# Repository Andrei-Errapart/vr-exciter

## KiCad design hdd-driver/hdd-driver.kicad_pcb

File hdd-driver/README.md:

# HDD spindle driver board

A carrier PCB that screws to the underside of the gutted 3.5" hard drive. It
drives the spindle motor through the drive's own **spring contacts**, so the
magnet disc in `../disk/` can spin at 3000 rpm.

- **MCU:** WeAct Studio STM32G474CEU6 **Core Board** (the square 36 × 28 mm
  board), on sockets.
- **Motor driver:** SimpleFOC Mini v1.0 (TI DRV8313), on sockets, driven in
  3-PWM mode from TIM1.
- **Motor supply:** external 12 V on a screw terminal, or USB through an
  MT3608 boost module (5 V → 12 V). Jumper JP1 selects between them.
- **Supply monitor:** VM ÷ 11 into an ADC pin.
- **Current sensing:** VM bus current (INA181) and inline phase A/B current
  (two INA240), all into ADC pins.
- **Speed/angle pickup:** input for a VR (variable reluctance) pickup coil
  under the magnet disc, into a comparator and ADC pin.

KiCad 10 project: `hdd-driver.kicad_pro`. The schematic passes ERC with 0
violations. The PCB is fully routed: DRC reports 0 unconnected items. The
remaining DRC errors are the C2/U2 courtyard overlap and U3 in the edge
keepout, plus silkscreen warnings.

## Files

| Path | Content |
|------|---------|
| `hdd-driver.kicad_sch`, `.kicad_pcb`, `.kicad_pro` | Schematic and PCB. They were generated once by script and are now the source: edit them in KiCad. |
| `sym-lib-table`, `fp-lib-table` | Project libraries `hdd-driver` (paths use `${KIPRJMOD}`) |
| `lib/hdd-driver.kicad_sym` | Symbols: `WeAct_STM32G474_CoreBoard`, `SimpleFOC_Mini_v1.0`, `MT3608_Boost_Module`, `HDD_Motor_SpringContacts` |
| `lib/hdd-driver.pretty/` | Footprints for those parts, plus `MountingHole_2.4mm_M2_Pad` and `MountingHole_3.2mm_M3_Pad` |
| `lib/3d/*.step` | Module models (WeAct, SimpleFOC Mini, MT3608) with pins-down headers |
| `lib/3d/src/` | WeAct's original STEP, the same STEP with its headers stripped, and the KiCad source boards the module models are exported from |
| `Export_HddDriver_V1_zip` | JLCPCB manufacturing package; see [Regenerating generated files](#regenerating-generated-files) |
| `scripts/export-test-model` | Fit-test 3D models; see [Checking the fit](#checking-the-fit) |
| `scripts/module-models/` | Regenerates `lib/3d/*.step` (`make-module-models`) |
| `scripts/library/` | Generators that made the symbols and footprints, plus a small S-expression helper. Rerunning them overwrites edits made in KiCad. |
| `scripts/photo/rectify_underside.py` | The photo measurement behind the board geometry |
| `doc/` | Images: candidate holes, outline options, final layout on the photo |

## Mechanics

### Drive frame

All drive positions are in a **drive frame**: a bottom view as photographed,
with the connector end at the top.

- **X** runs to the right from the drive's centre line.
- **Y** runs down from the connector end.
- The PCB's aux and grid origins sit at the drive-frame origin, which is
  KiCad position (150, 40) mm. Set the KiCad coordinate display to the grid
  origin and positions read directly in this frame.

The positions come from `../disk/hdd-photos/07-hdd-underside-width-ruler.jpg`.
That photo is taken at an angle, and its rulers lie about 26 mm below the
underside of the drive, so ruler scale is no use here (on the rectified image
the rulers read about 2 % short). Instead, the photo was rectified with a
homography fitted to the four **SFF-8301 bottom mounting holes**. Those holes
are 95.25 mm apart across the drive, 41.28 mm from the connector end, with
the second pair 44.45 mm further down. Expect about ±0.5 mm on the features
below. `scripts/photo/rectify_underside.py` has the method and the pixel
data.

| Feature | X | Y | Notes |
|---|---|---|---|
| Screw hole 2 | 16.69 | 15.29 | M2, holds the PCB |
| Screw hole 3 | 16.73 | 31.27 | M2, holds the PCB |
| Screw hole 7 | −9.05 | 56.92 | M2, holds the PCB **and** the spring-contact block |
| Screw hole 8 | 31.29 | 62.90 | M2, holds the PCB |
| Screw holes 1, 6 | −43.37 / −42.58 | 17.63 / 63.39 | Not used: a plain rectangle cannot reach them without a notch around SFF hole 4 |
| SFF holes 4, 5, 9, 10 | ±47.625 | 41.28 / 85.73 | Drive mounting holes (6-32) on the side rails; outside the PCB |
| Spring contacts 1–3 (tips) | −11.83 / −9.83 / −7.87 | 63.67 / 63.17 / 62.60 | 2.0 mm pitch, about 6.0 mm from screw 7, strip turned 13.5° |
| Spindle axis | 0.2 | 95.9 | The large circle (R ≈ 20) |

`doc/hdd-underside-candidate-holes.jpg` shows the hole numbering.

### PCB

- **Outline:** a plain rectangle, X −36…38 and Y 0…73 (74 × 73 mm), 1.6 mm
  thick. It started as option B in `doc/outline-options.jpg` (Y 12…88). The
  first test print showed that the bottom edge sat on the motor, so the
  outline moved 15 mm towards the connector end. It now ends about 3 mm short
  of the motor circle. The top edge used to reach 3 mm past the drive's
  connector end; it was cut back to sit flush with it. The sides still clear
  the rail bulges around SFF holes 4 and 5.
- **Edge keepout:** component courtyards stay 1 mm clear of the board edge.
  The rule area `EdgeKeepout` (a 1 mm frame inside the outline) and the
  custom rule in `hdd-driver.kicad_dru` enforce this in DRC. Footprints
  excluded from the BOM (the mounting holes and other copper-only parts) are
  exempt.
- **GND pours:** `GND_TOP` on F.Cu and `GND_BOTTOM` on B.Cu cover the whole
  board (0.3 mm clearance, thermal reliefs). The rule area
  `J2_SpringKeepout` (J2's B.CrtYd) keeps the bottom pour and vias away from
  the spring pads. 0.6/0.3 mm GND stitching vias run about every 5 mm round
  the edge and on a 10 mm grid inside, only where both pours have copper.
- **Mounting:** four M2 screws in holes 2, 3, 7 and 8. Holes are 2.4 mm
  (ISO 273 medium fit), plated with a 4.2 mm pad, and tied to GND.
- **Corner holes H4–H7:** M3 (3.2 mm, plated, 6.4 mm pad, on GND), 4 mm in
  from each edge, at X −32 / 34 and Y 4 / 69. They are optional: for rubber
  feet, or for spacers to a housing. H6/H7 courtyards are kept free of parts
  on both sides. Since the top edge was cut back, H4 and H5 overlap the
  courtyards of U1 (WeAct) and U3 (MT3608); DRC reports this, and it is
  still open.
- **Spring contacts:** footprint `HDD_SpringContacts_3P_P2.0mm`, placed on
  screw 7 and rotated 13.5°. Three 1.4 × 4.0 mm pads on **B.Cu**, the side
  facing the drive. The pad centres lie within 0.2 mm of the measured spring
  tips. Order the board with ENIG (gold) finish for these pads.
- **Modules** on top, away from the drive:
  - WeAct board at the top left, with its USB-C facing the left edge.
  - MT3608 upright at the right, between holes 2/3 and the edge.
  - SimpleFOC Mini in the lower middle, between the MT3608 and hole 8,
    turned 180°.
  - JP1 between the WeAct board and holes 2/3; C1 and C2 next to the
    SimpleFOC `+` pad.
  - The 12 V screw terminal J1 at the lower left, wire entry facing out,
    with D1 beside it.
- **Stacking heights:**
  - 2×12, 2×5, 1×3 and 1×1 female sockets: 8.5 mm.
  - Male header plastic on the modules: 2.54 mm.
  - So each module PCB sits 11.04 mm above the carrier.
  - The MT3608 sits on its pins, 2.54 mm above the carrier.
  - The highest point is the WeAct board, about 16 mm above the carrier's
    top surface; the MT3608 trimmer reaches about 15 mm.
  - The drive needs feet at least that high when it stands on its underside.

## Electronics

```
J1 12V IN ─ D1 SS54 ─┬─ +12V ── JP1.1 ┐
 (reverse polarity)  │                ├─ JP1.2 = VM ─┬─ RS1 20 mΩ ─ VM_DRV ─┬─ SimpleFOC "+" ── DRV8313 VM
                     │   VBOOST ─ JP1.3 ┘            │  (U4 INA181: I_BUS)  └─ C1 470 µF + C2 100 nF
                     │      ▲                        └─ R1 100k / R2 10k ─ VM_SENSE ─ PA0
                     │   U3 MT3608 (set to 12 V)
                     │      ▲
                     └─ D2 B5819W ─ VCC_MCU ─ WeAct VCC (LDO input, 3.3–20 V)
                                    ▲
                     USB VBUS ─ WeAct's own B5819W ┘
```

- **JP1 1-2:** the motor runs from the external 12 V. D2 also feeds the WeAct
  `VCC`, so the MCU runs without USB. WeAct's own VBUS diode keeps the 12 V
  away from the USB host.
- **JP1 2-3:** the motor runs from USB. WeAct `VCC` (VBUS minus a Schottky
  drop, about 4.6 V) feeds the MT3608, and its 12 V output becomes VM. **Set
  the trimmer to 12 V before fitting the jumper.** The DRV8313 needs
  VM ≥ 8 V (UVLO), so USB 5 V can't drive it directly. USB current (and the
  1 A WeAct diode) limit the motor power in this mode.

| Signal | MCU pin (WeAct header) | SimpleFOC Mini | Notes |
|---|---|---|---|
| DRV_IN1 | PA8, TIM1_CH1 AF6 (P1.10) | IN1 (H1 pin 3) | |
| DRV_IN2 | PA9, TIM1_CH2 AF6 (P1.11) | IN2 (5) | |
| DRV_IN3 | PA10, TIM1_CH3 AF6 (P1.12) | IN3 (7) | |
| DRV_EN | PB12 (P1.5) | EN (9) | 10 kΩ into EN1–3, 100 kΩ pull-downs: the driver is off at reset |
| DRV_nFAULT | PB13 (P1.6) | nFT (10) | Open drain, 10 kΩ pull-up on the module |
| DRV_nSLEEP | PB14 (P1.7) | nSP (8) | |
| DRV_nRESET | PB15 (P1.8) | nRT (6) | |
| VM_SENSE | PA0, ADC1_IN1 (P2.20) | — | VM / 11; 35 V gives 3.18 V |
| PH_A/B/C | — | M1/M2/M3 | To the spring pads, A and B through RS2/RS3. Phase order only sets the direction of rotation. |
| I_A | PA2, ADC1_IN3 (P2.18) | — | Phase A current (U5 INA240A1, RS2 20 mΩ): 1.65 V − 0.4 V/A (inverted, see below), ±4 A |
| I_B | PA4, ADC2_IN17 (P2.16) | — | Phase B current (U6, RS3): same scale. On ADC2, so it can be sampled together with I_A in dual mode. |
| I_BUS | PA3, ADC1_IN4 (P2.15) | — | VM bus current (U4 INA181A2, RS1 20 mΩ): 1 V/A, 0–3.3 A, after C1/C2 so it is averaged |
| VR_IN | PA1, COMP1_INP / ADC12_IN2 (P2.17) | — | VR pickup coil on J3, biased to 1.65 V, 22 kΩ + BAV99 clamp, 470 pF |

- **SimpleFOC:** `BLDCDriver3PWM driver(PA8, PA9, PA10, PB12);`. The HDD
  motor has no sensors, so start with open-loop velocity control. Then:
  1. Close a speed loop on the VR pickup (60 pulses/rev). It also detects a
     stall.
  2. Use the VR pulses as a position sensor and run FOC in voltage mode.
     The VR coil gives no signal at standstill, so start open-loop and switch
     over once the pulses are steady.
- **Current sensing:** `InlineCurrentSense` with 0.02 Ω on PA2 and PA4
  (phase C unmeasured). Use gain **−20 for A** and +20 for B: U5's inputs are
  swapped for the layout, so I_A reads with the opposite sign. The INA240 rejects the PWM common-mode swing,
  so it can sample at any point of the PWM cycle. RS1/U4 measure the
  averaged supply current: use it for stall and overload detection.
- **VR input:** one coil end sits at `VR_BIAS` (1.65 V, R7/R8/C8), the other
  goes through R6 22 kΩ to `VR_IN`. The BAV99 clamps `VR_IN` to the rails;
  22 kΩ keeps the clamp current at about 2 mA even for a 50 V peak. Use COMP1
  (`VR_IN` on its INP pin, an internal DAC3 channel as threshold, hysteresis
  on) and route its output to a timer input capture. The same pin is on
  ADC12_IN2 for looking at the raw waveform.
- **Phase current:** an HDD spindle motor has only a few ohms per phase.
  Keep `voltage_limit` low, or the DRV8313 overcurrent protection
  (3 A min / 5 A typ) will trip.
- **Module 3V3:** the SimpleFOC Mini's `3V3` is the DRV8313's 10 mA
  regulator output. It is left unconnected.
- **More pin facts:** `../datasheets/weact_stm32G474/README.md` (WeAct board)
  and `../datasheets/drv8313/README.md` (SimpleFOC Mini).

## Checking the fit

```sh
scripts/export-test-model                  # -> build/test-model/
scripts/export-test-model --thickness 2.4  # stiffer print, same hole positions
```

This makes a copy of the PCB with the three spring pads replaced by
through-slots of the same size and angle, and exports:

- `test-board.stl` / `test-board.step`: the bare board with every hole, in
  drive-frame coordinates.
- `test-assembly.step`: the board with the module models.

To check:

1. Print `test-board.stl`.
2. Screw it on with the M2 screws in holes 2, 3, 7 and 8.
3. Look through the slots: each spring tip should sit in the middle of its
   slot, and the print should lie flat.

If something is off, move the parts in the PCB rather than in the scripts.
The spring pads belong to footprint J2; move or rotate J2 around screw 7.
The holes are H1, H2 and H3.

The first print (2026-10-25) confirmed the four M2 holes and the three
spring slots. The outline was then moved 15 mm away from the motor; see
[PCB](#pcb).

## Before ordering

- [x] Test print: M2 holes and spring slots fit (first print).
- [ ] Reprint after the outline move: the bottom edge clears the motor, and
      the top edge past the connector end touches nothing.
- [ ] **Bottom side faces the metal base.** Socket and terminal leads stick
      out about 1.5 mm, and the board sits flat against the bosses. Either
      cut the leads flush and insulate the bottom (Kapton), or check on the
      test print where the base is recessed. Raising the board on spacers
      would also lift it off the springs.
- [ ] MT3608 pad positions: modules differ between vendors. Measure yours
      against footprint `MT3608_Boost_Module` (VIN−/VIN+ 7.87 mm apart,
      31.2 mm between input and output pads).
- [ ] Route the board. Use wide traces (≥ 0.8 mm) for VM, GND and PH_A/B/C,
      and GND pours on both layers, kept clear of the spring pads.
- [ ] Confirm that the J1 screw terminal's wire entry faces the board edge in
      the 3D view. (J3, the VR coil terminal, faces the right edge.)
- [x] Route the current-sense and VR parts. The shunt areas are routed by hand
      and their tracks are **locked**. Each INA input runs on its own track to
      its shunt pad (Kelvin), so trace resistance doesn't add to the 20 mΩ.
      The rest was routed with KiCadRoutingTools (see [Routing](#routing)).
- [ ] VR pickup coil: check that its pole face is narrower than the magnet
      pitch (10 mm), with the long side radial.

## Routing

The board was routed in two steps:
1. **By hand** (locked tracks):
   - The three shunts with their Kelvin sense legs.
   - PH_A/PH_B from the SimpleFOC pads through RS2/RS3 to J2. They run on
     B.Cu below the spring pads and enter them from the lower end. The vias
     sit outside `J2_SpringKeepout`.
   - The VM/VM_DRV stubs at RS1.
2. **The rest** with
   [KiCadRoutingTools](https://github.com/drandyhaas/KiCadRoutingTools),
   using KiCad's bundled Python:

   ```sh
   python3 py_router/route.py hdd-driver.kicad_pcb routed.kicad_pcb \
     --nets /3V3 /I_A /I_B /I_BUS /VR_IN /VR_P /VR_BIAS GND \
     --track-width 0.3 --power-nets /3V3 --power-nets-widths 0.4 \
     --keep-input-copper --write-fill --same-net-pad-clearance 0.2 --fab-tier standard
   ```

   Run it on a copy. Afterwards:
   - Set its 0.45 mm vias to 0.5/0.3 mm (the project minimum).
   - Move any via off a pad.
   - Give GND pads with a one-spoke thermal a solid zone connection.
   - Copy the board back, but not the `.kicad_pro`: the router lowers
     `min_hole_clearance` to 0.2 mm in its copy.

   Don't autoroute the shunt nets (PH_A/B, PH_A/B_DRV, VM, VM_DRV). The
   router doesn't know about Kelvin connections, and in a trial it joined
   three of the six sense inputs onto the high-current path.

## Regenerating generated files

| What | Command | Needs |
|---|---|---|
| JLCPCB order package | `./Export_HddDriver_V1_zip` writes `HddDriver_V1_<date>.zip` (Gerbers, drills, JLCPCB BOM/CPL, PDFs, STEP, order notes). It runs ERC and DRC first and works on a copy of the board. | KiCad 10, python3, zip. LCSC part numbers are in the script. |
| Fit-test models | `scripts/export-test-model` | KiCad 10 (`kicad-cli` and its bundled Python) |
| Module STEP models | `scripts/module-models/make-module-models` | KiCad 10. Add `--strip` with `OCP_PYTHON=<python with cadquery-ocp>` to redo the WeAct header stripping. |
| Symbols / footprints | `python3 scripts/library/gen_symbols.py`, KiCad Python `scripts/library/gen_footprints.py` | Overwrites lib edits |
| Photo measurement | `python3 scripts/photo/rectify_underside.py PHOTO [OUT.png]` | opencv-python, numpy |

The schematic and PCB were made by one-off scripts that are not kept here.
Edit them in KiCad.

## Sources

- **SFF-8301 Rev 1.9** (3.5" form factor):
  https://members.snia.org/document/dl/25862
- **WeAct STM32G474 Core Board:**
  https://github.com/WeActStudio/WeActStudio.STM32G474CoreBoard, via
  `../datasheets/weact_stm32G474/`
- **SimpleFOC Mini v1.0:** https://github.com/simplefoc/SimpleFOCMini (tag
  `v1.0`), via `../datasheets/drv8313/`
- **MT3608 module drawing:**
  https://components101.com/modules/mt3608-2a-dc-dc-step-up-power-module

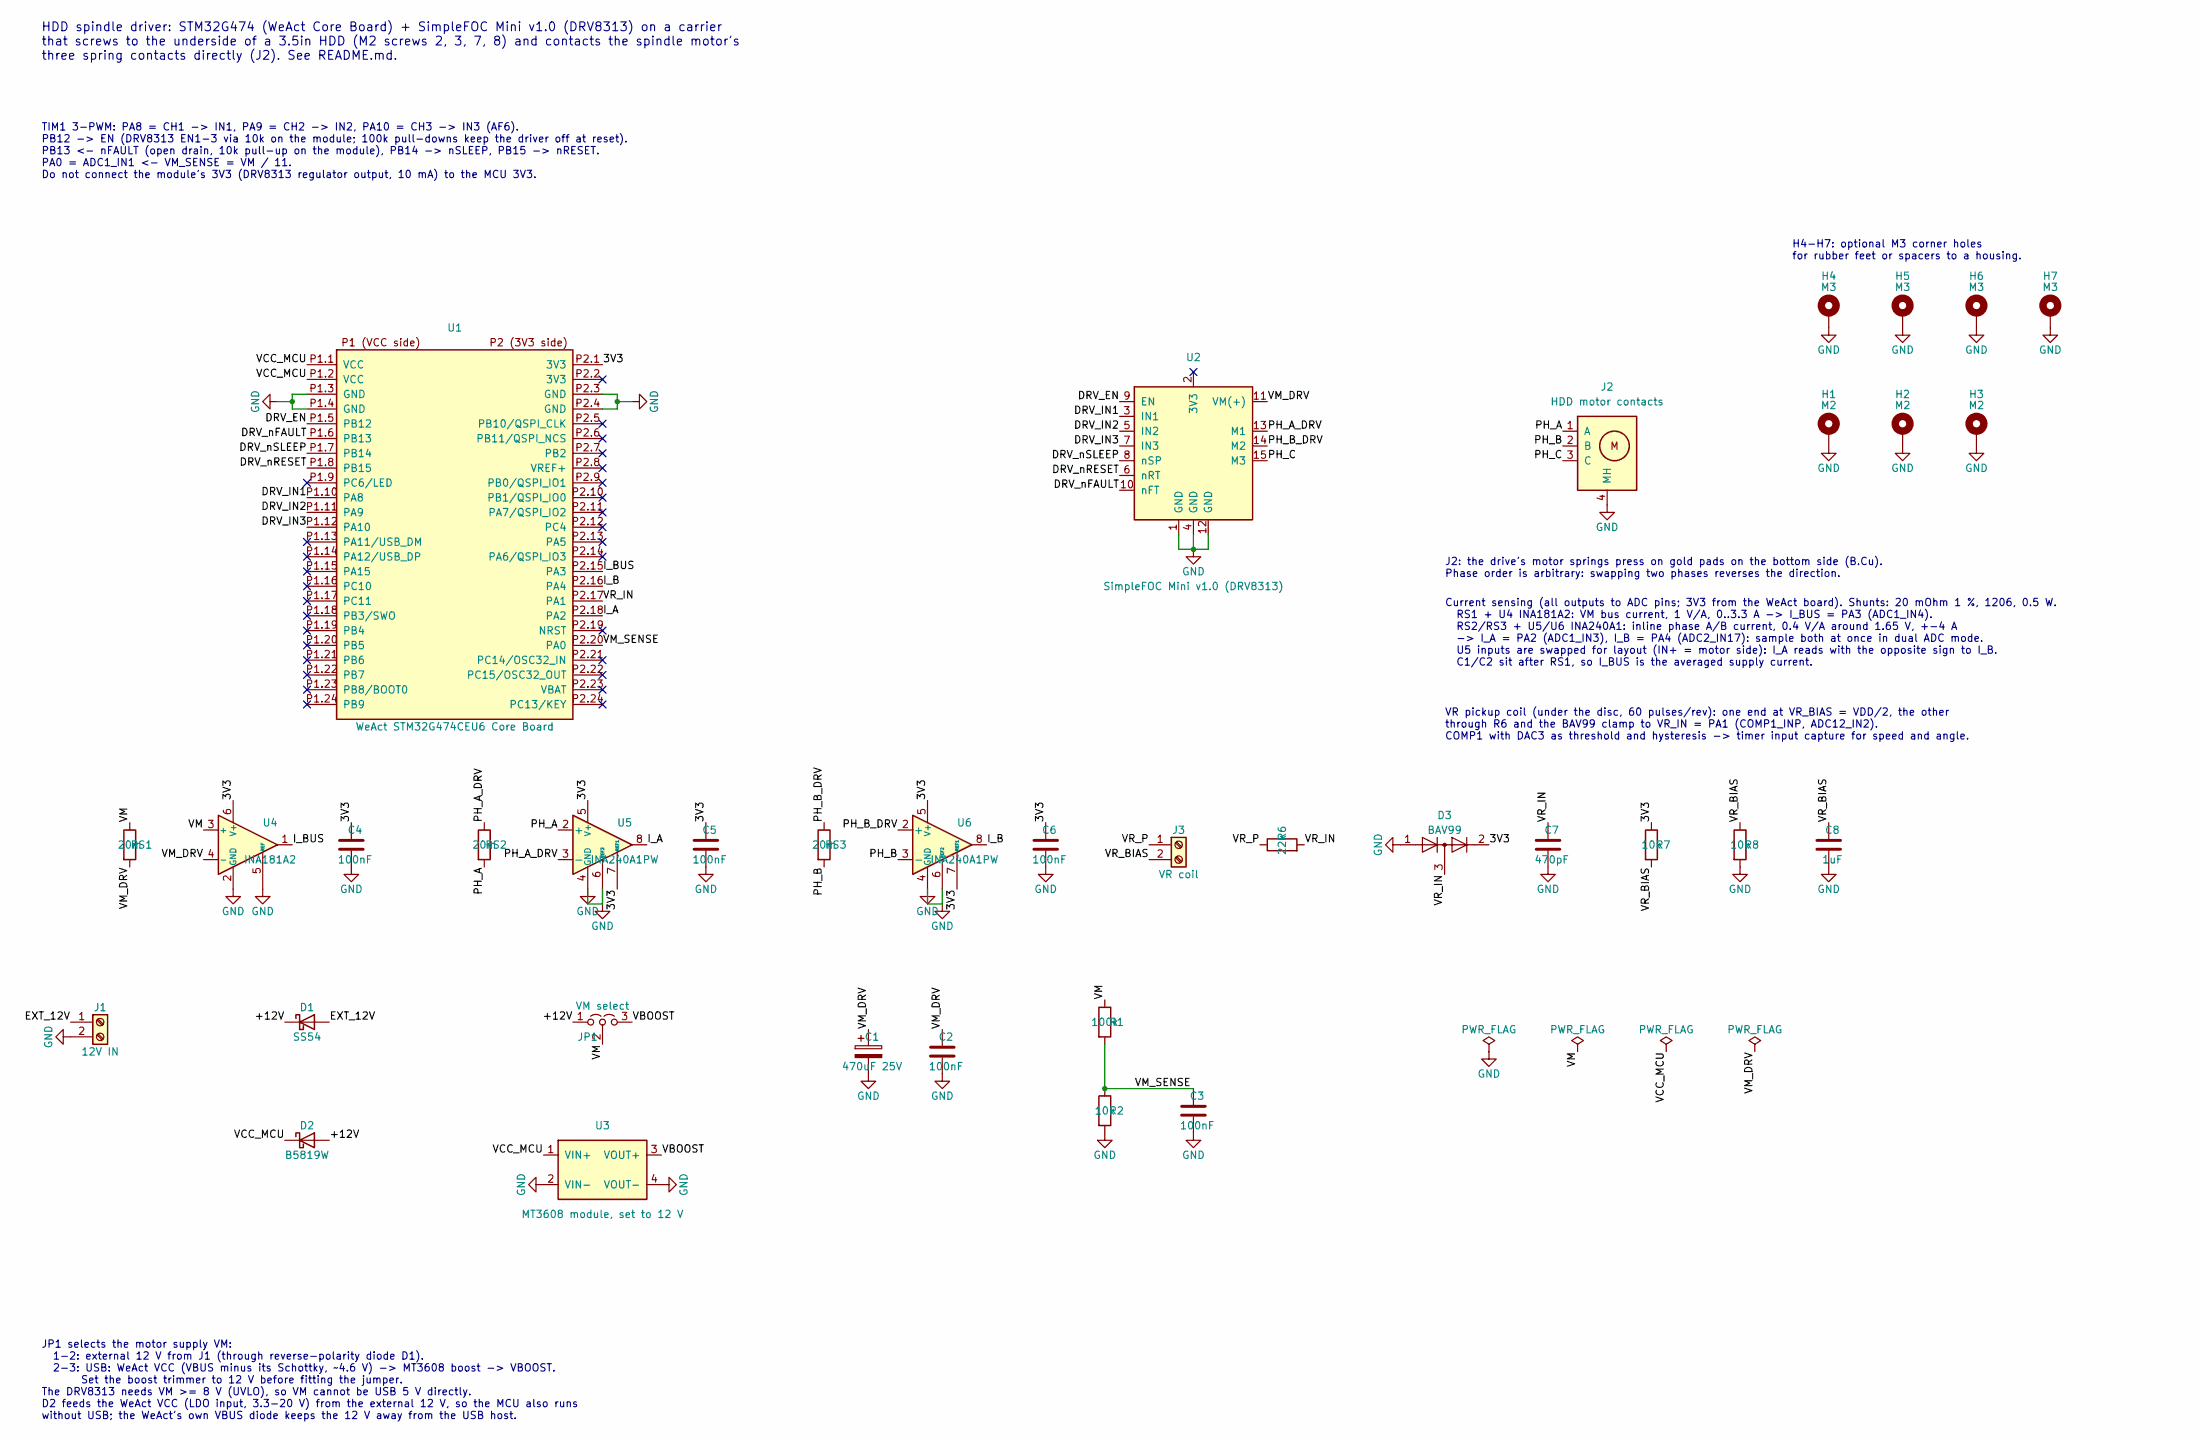
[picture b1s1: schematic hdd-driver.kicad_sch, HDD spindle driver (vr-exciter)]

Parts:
C1: 470uF 25V; CP_Radial_D8.0mm_P3.50mm
C2, C3, C4, C5, C6: 100nF; C_0603_1608Metric
C7: 470pF; C_0603_1608Metric
C8: 1uF; C_0603_1608Metric
D1: SS54; D_SMA
D2: B5819W; D_SOD-123
D3: BAV99; SOT-23
H1, H2, H3: M2; MountingHole_2.4mm_M2_Pad
H4, H5, H6, H7: M3; MountingHole_3.2mm_M3_Pad
J1: 12V IN; TerminalBlock_Phoenix_MKDS-1,5-2-5.08_1x02_P5.08mm_Horizont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
J2: HDD motor contacts; HDD_SpringContacts_3P_P2.0mm
J3: VR coil; TerminalBlock_Phoenix_MPT-0,5-2-2.54_1x02_P2.54mm_Horizontal
JP1: VM select; PinHeader_1x03_P2.54mm_Vertical
R1: 100k; R_0603_1608Metric
R2, R7, R8: 10k; R_0603_1608Metric
R6: 22k; R_0603_1608Metric
RS1, RS2, RS3: 20m; R_1206_3216Metric
U1: WeAct STM32G474CEU6 Core Board; WeAct_STM32G474_CoreBoard_Socketed
U2: SimpleFOC Mini v1.0 (DRV8313); SimpleFOC_Mini_v1.0_Socketed
U3: MT3608 module, set to 12 V; MT3608_Boost_Module
U4: INA181A2; SOT-23-6
U5, U6: INA240A1PW; TSSOP-8_4.4x3mm_P0.65mm

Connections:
/3V3: C4.1, C5.1, C6.1, D3.2 (A), R7.1, U1.P2.1 (3V3), U4.6 (V+), U5.5 (V+), U5.7 (REF1), U6.5 (V+), U6.7 (REF1)
/+12V: D1.1 (K), D2.2 (A), JP1.1 (A)
/DRV_EN: U1.P1.5 (PB12), U2.9 (EN)
/DRV_IN1: U1.P1.10 (PA8), U2.3 (IN1)
/DRV_IN2: U1.P1.11 (PA9), U2.5 (IN2)
/DRV_IN3: U1.P1.12 (PA10), U2.7 (IN3)
/DRV_nFAULT: U1.P1.6 (PB13), U2.10 (nFT)
/DRV_nRESET: U1.P1.8 (PB15), U2.6 (nRT)
/DRV_nSLEEP: U1.P1.7 (PB14), U2.8 (nSP)
/EXT_12V: D1.2 (A), J1.1
/I_A: U1.P2.18 (PA2), U5.8
/I_B: U1.P2.16 (PA4), U6.8
/I_BUS: U1.P2.15 (PA3), U4.1
/PH_A: J2.1 (A), RS2.2, U5.2 (+)
/PH_A_DRV: RS2.1, U2.13 (M1), U5.3 (-)
/PH_B: J2.2 (B), RS3.2, U6.3 (-)
/PH_B_DRV: RS3.1, U2.14 (M2), U6.2 (+)
/PH_C: J2.3 (C), U2.15 (M3)
/VBOOST: JP1.3 (B), U3.3 (VOUT+)
/VCC_MCU: D2.1 (K), U1.P1.1 (VCC), U1.P1.2 (VCC), U3.1 (VIN+)
/VM: JP1.2 (C), R1.1, RS1.1, U4.3 (+)
/VM_DRV: C1.1, C2.1, RS1.2, U2.11 (VM(+)), U4.4 (-)
/VM_SENSE: C3.1, R1.2, R2.1, U1.P2.20 (PA0)
/VR_BIAS: C8.1, J3.2, R7.2, R8.1
/VR_IN: C7.1, D3.3 (K), R6.2, U1.P2.17 (PA1)
/VR_P: J3.1, R6.1
GND: C1.2, C2.2, C3.2, C4.2, C5.2, C6.2, C7.2, C8.2, D3.1 (K), H1.1, H2.1, H3.1, H4.1, H5.1, H6.1, H7.1, J1.2, J2.4 (MH), R2.2, R8.2, U1.P1.3 (GND), U1.P1.4 (GND), U1.P2.3 (GND), U1.P2.4 (GND), U2.1 (GND), U2.4 (GND), U2.12 (GND), U3.2 (VIN-), U3.4 (VOUT-), U4.2 (GND), U4.5 (REF), U5.1 (GND), U5.4 (GND), U5.6 (REF2), U6.1 (GND), U6.4 (GND), U6.6 (REF2)

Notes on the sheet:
HDD spindle driver: STM32G474 (WeAct Core Board) + SimpleFOC Mini v1.0 (DRV8313) on a carrier that screws to the underside of a 3.5in HDD (M2 screws 2, 3, 7, 8) and contacts the spindle motor's three spring contacts directly (J2). See README.md.
TIM1 3-PWM: PA8 = CH1 -> IN1, PA9 = CH2 -> IN2, PA10 = CH3 -> IN3 (AF6). PB12 -> EN (DRV8313 EN1-3 via 10k on the module; 100k pull-downs keep the driver off at reset). PB13 <- nFAULT (open drain, 10k pull-up on the module), PB14 -> nSLEEP, PB15 -> nRESET. PA0 = ADC1_IN1 <- VM_SENSE = VM / 11. Do n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
JP1 selects the motor supply VM: 1-2: external 12 V from J1 (through reverse-polarity diode D1). 2-3: USB: WeAct VCC (VBUS minus its Schottky, ~4.6 V) -> MT3608 boost -> VBOOST. Set the boost trimmer to 12 V before fitting the jumper. The DRV8313 needs VM >= 8 V (UVLO), so VM cannot be USB 5 V dire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
J2: the drive's motor springs press on gold pads on the bottom side (B.Cu). Phase order is arbitrary: swapping two phases reverses the direction.
H4-H7: optional M3 corner holes for rubber feet or spacers to a housing.
Current sensing (all outputs to ADC pins; 3V3 from the WeAct board). Shunts: 20 mOhm 1 %, 1206, 0.5 W. RS1 + U4 INA181A2: VM bus current, 1 V/A, 0..3.3 A -> I_BUS = PA3 (ADC1_IN4). RS2/RS3 + U5/U6 INA240A1: inline phase A/B current, 0.4 V/A around 1.65 V, +-4 A -> I_A = PA2 (ADC1_IN3), I_B = PA4 (A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
VR pickup coil (under the disc, 60 pulses/rev): one end at VR_BIAS = VDD/2, the other through R6 and the BAV99 clamp to VR_IN = PA1 (COMP1_INP, ADC12_IN2). COMP1 with DAC3 as threshold and hysteresis -> timer input capture for speed and angle.

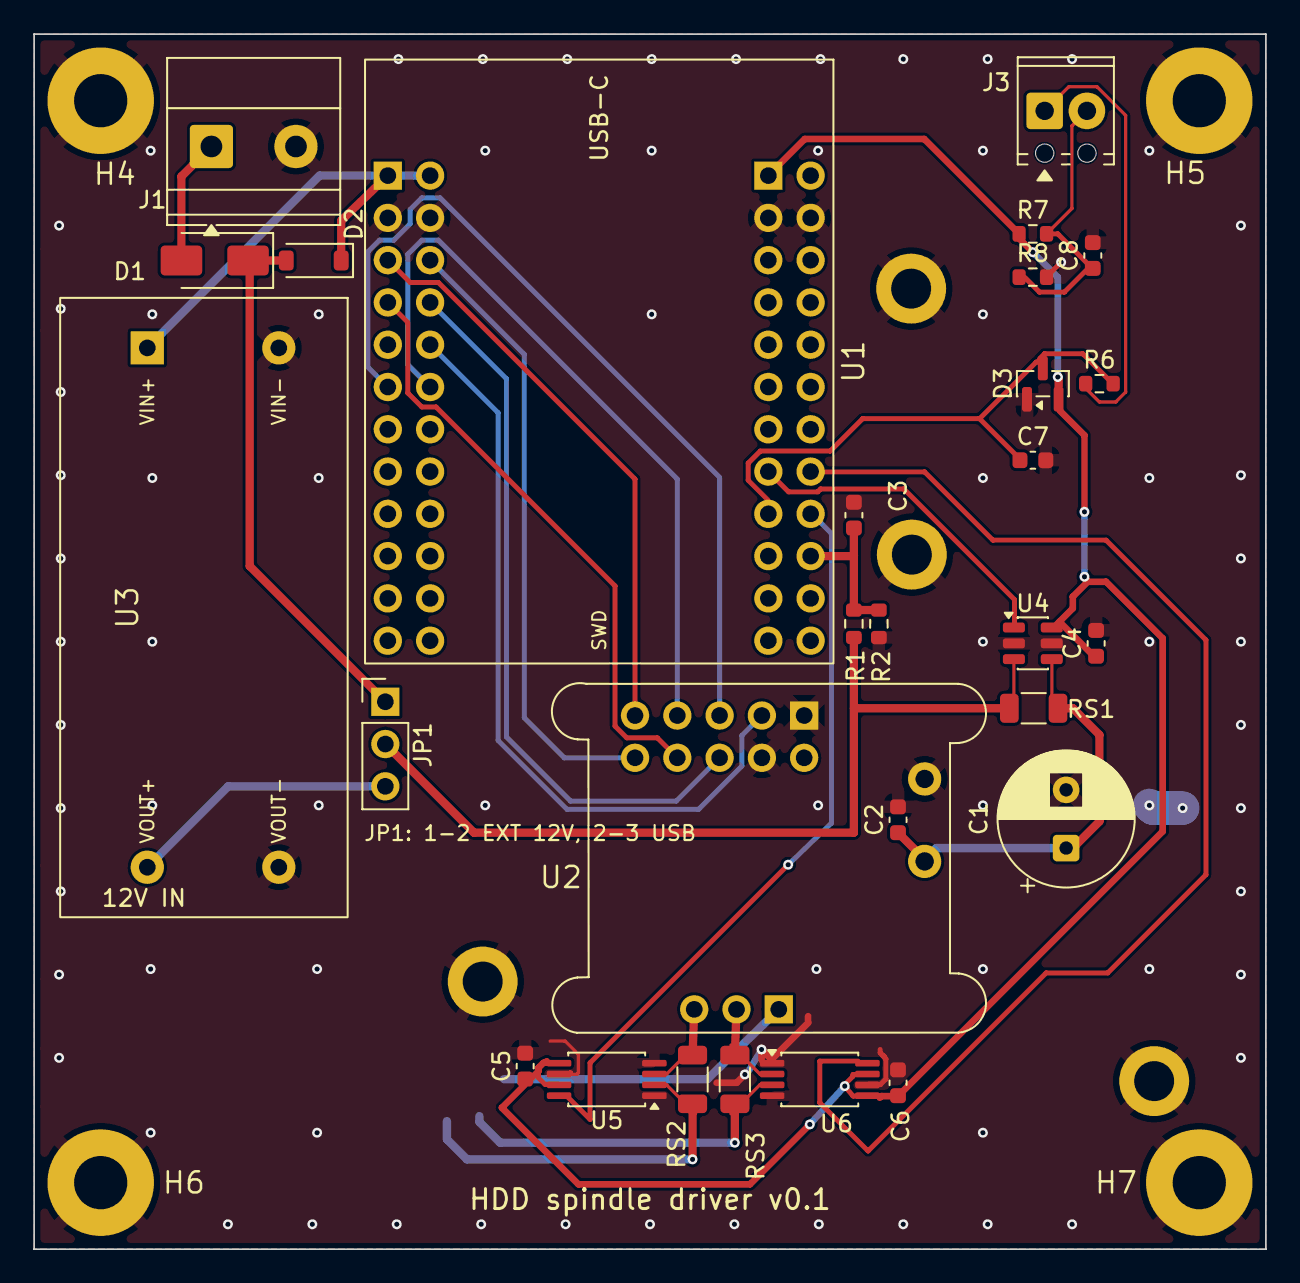
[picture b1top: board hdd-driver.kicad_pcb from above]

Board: 2 copper layers, 74.0 x 73.0 mm, 36 parts (0 on the bottom side), 27 nets.
